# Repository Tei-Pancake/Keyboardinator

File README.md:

# Keyboardinator

Welcome to the Keyboardinator repository.

The Keyboardinator is a small 3-key macropad I made because apparently having a normal keyboard wasn't enough. It's built around a XIAO RP2040, three mechanical switches, and a tiny OLED screen.

The idea is pretty simple: three keys, three shortcuts, and hopefully a little less clicking around.

### Keyboardinator Preview

**3D Model**

**PCB**

**Sexy Schema**

### What's inside?
3 mechanical switches for the actual button pressing stuff.
0.91" OLED display connected through I2C (GND, VCC, SCL, SDA).
Seeed Studio XIAO RP2040 as the brain of the whole thing.
KMK + CircuitPython for the firmware, because I wanted something I could mess around with without making my life unnecessarily difficult.

### What do the keys do?

Nothing too complicated:

Key 1 — Work Simulator: Win + D
Makes the desktop appear. Very useful. Definitely not suspicious.
Key 2 — History Cleaner: Ctrl + W
Closes the current browser tab.
Key 3 — Security Lock: Win + L
Locks the computer.

The OLED is there to show the current status/layer and also because a macropad with a tiny screen is cooler than one without it.

##  Bill of Materials
You can find the full list of components required for this project in the [BOM.md](BOM.md) file.

## Repository Structure
/CAD 
  3D files for the case. 

/PCB 
  KiCad project files. 

/Firmware 
  main.py and the KMK/CircuitPython stuff. 

/production 
  Final files for actually making the thing: Gerbers, STL files and a copy of main.py.

### why did I make this?

Mostly because I wanted to learn how the whole process works.

This project involves a bit of everything: designing the case, making the PCB, routing it, figuring out the electronics, writing the firmware, and then trying to make all of it work together without something exploding.

It's a tiny project, but that's kind of the point. I wanted something I could actually finish and hold in my hands instead of another project that lives forever in a folder called final_final_v3.

Anyway, that's the Keyboardinator.

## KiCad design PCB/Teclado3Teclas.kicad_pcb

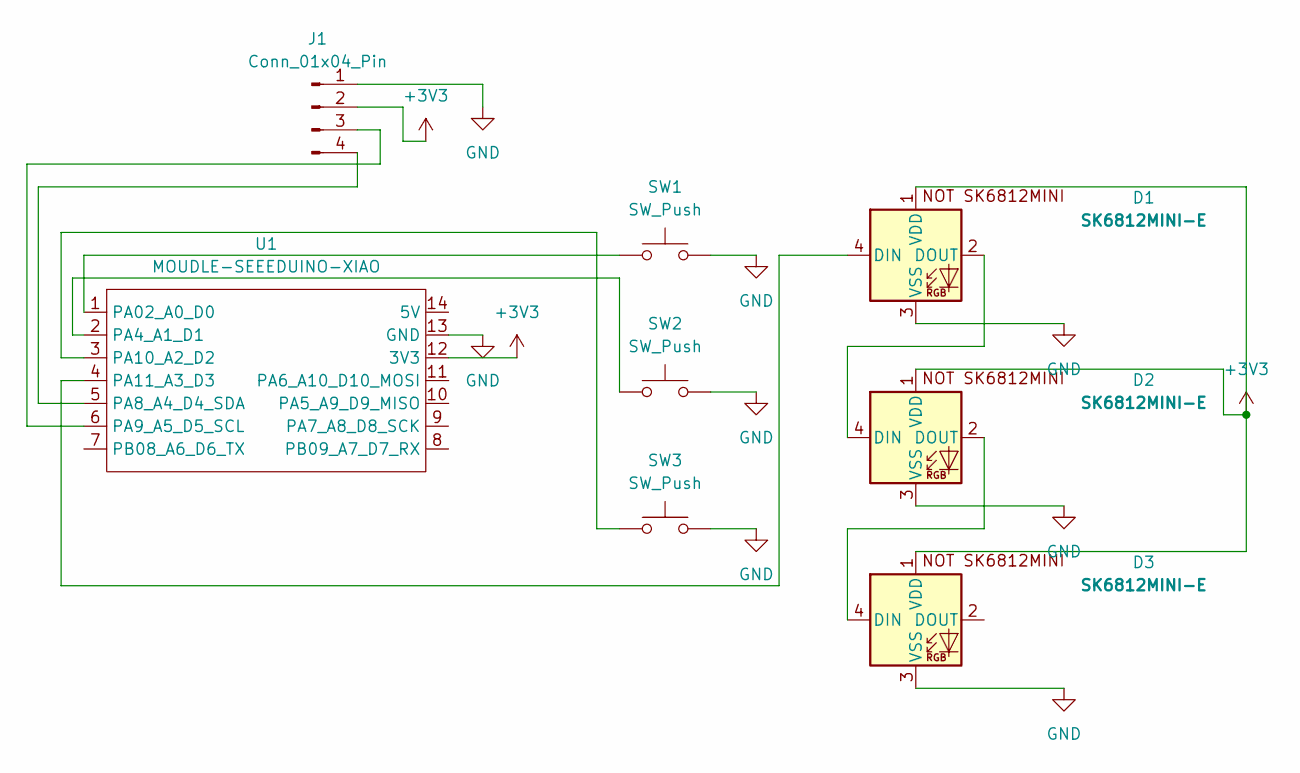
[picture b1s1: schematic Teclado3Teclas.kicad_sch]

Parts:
D1, D2, D3: SK6812MINI-E; SK6812MINI-E_fixed
J1: Conn_01x04_Pin; PinHeader_1x04_P2.54mm_Vertical
SW1, SW2, SW3: SW_Push; SW_Cherry_MX_1.00u_PCB
U1: MOUDLE-SEEEDUINO-XIAO; XIAO-Generic-Hybrid-14P-2.54-21X17.8MM

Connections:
+3V3: D1.1 (VDD), D2.1 (VDD), D3.1 (VDD), J1.2, U1.12 (3V3)
GND: D1.3 (VSS), D2.3 (VSS), D3.3 (VSS), J1.1, SW1.2, SW2.2, SW3.2, U1.13 (GND)
unnamed: D1.4 (DIN), U1.4 (PA11_A3_D3)
unnamed: D1.2 (DOUT), D2.4 (DIN)
unnamed: D2.2 (DOUT), D3.4 (DIN)
unnamed: J1.3, U1.6 (PA9_A5_D5_SCL)
unnamed: J1.4, U1.5 (PA8_A4_D4_SDA)
unnamed: SW1.1, U1.1 (PA02_A0_D0)
unnamed: SW2.1, U1.2 (PA4_A1_D1)
unnamed: SW3.1, U1.3 (PA10_A2_D2)

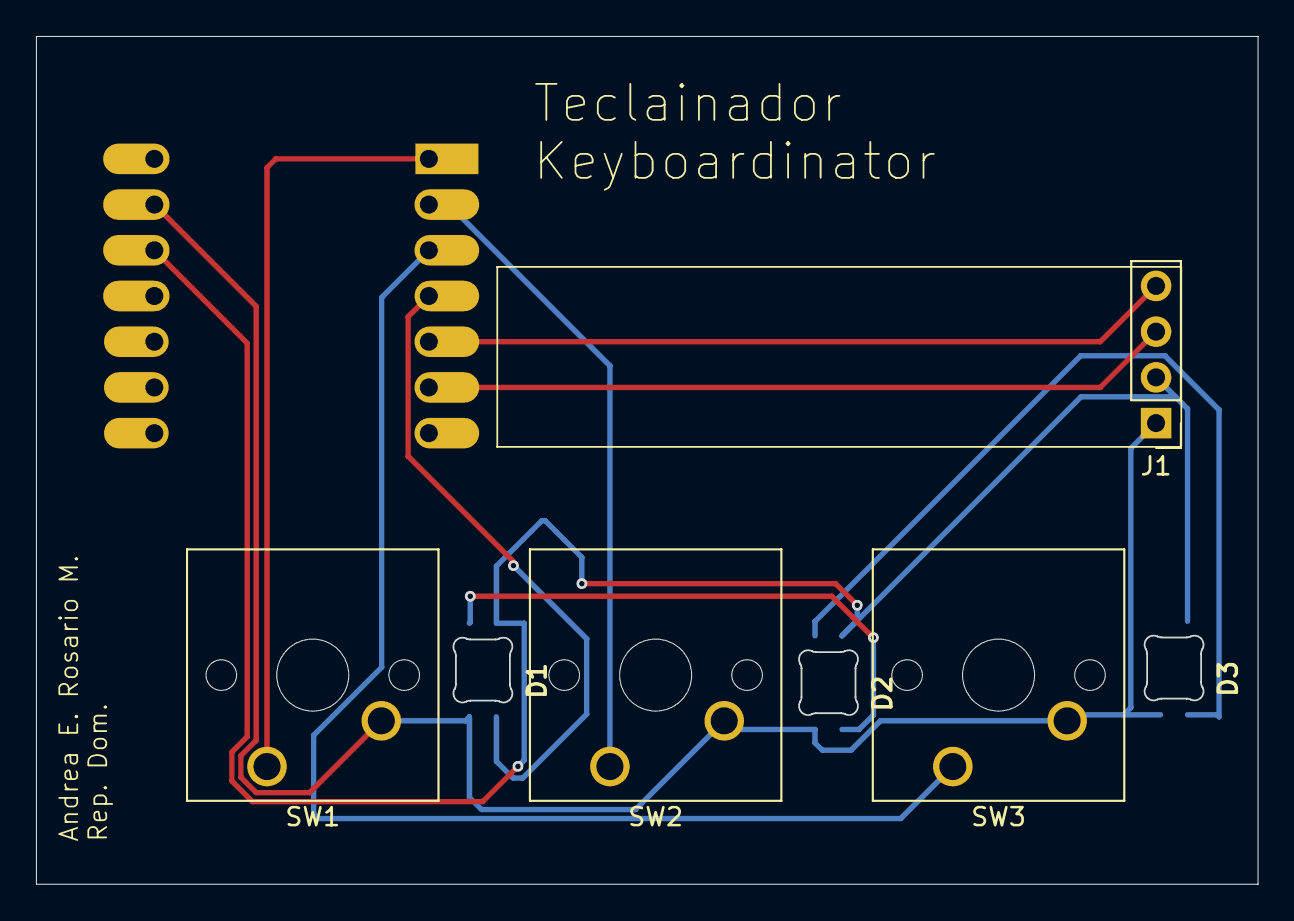
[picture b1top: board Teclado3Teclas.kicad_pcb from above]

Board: 2 copper layers, 67.8 x 47.0 mm, 8 parts (1 on the bottom side), 10 nets.

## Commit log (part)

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2026-06-18 Actualización: Reubicación de pantalla OLED y nuevos Gerbers
2026-06-18 Initial README in English
2026-06-27 Devlog: ¡Carcasa 3D lista, serigrafía personalizada y orden total!
